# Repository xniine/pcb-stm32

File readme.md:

## A modified version of PCB to work with stm32-vserprog (to support 1.8v SPI)

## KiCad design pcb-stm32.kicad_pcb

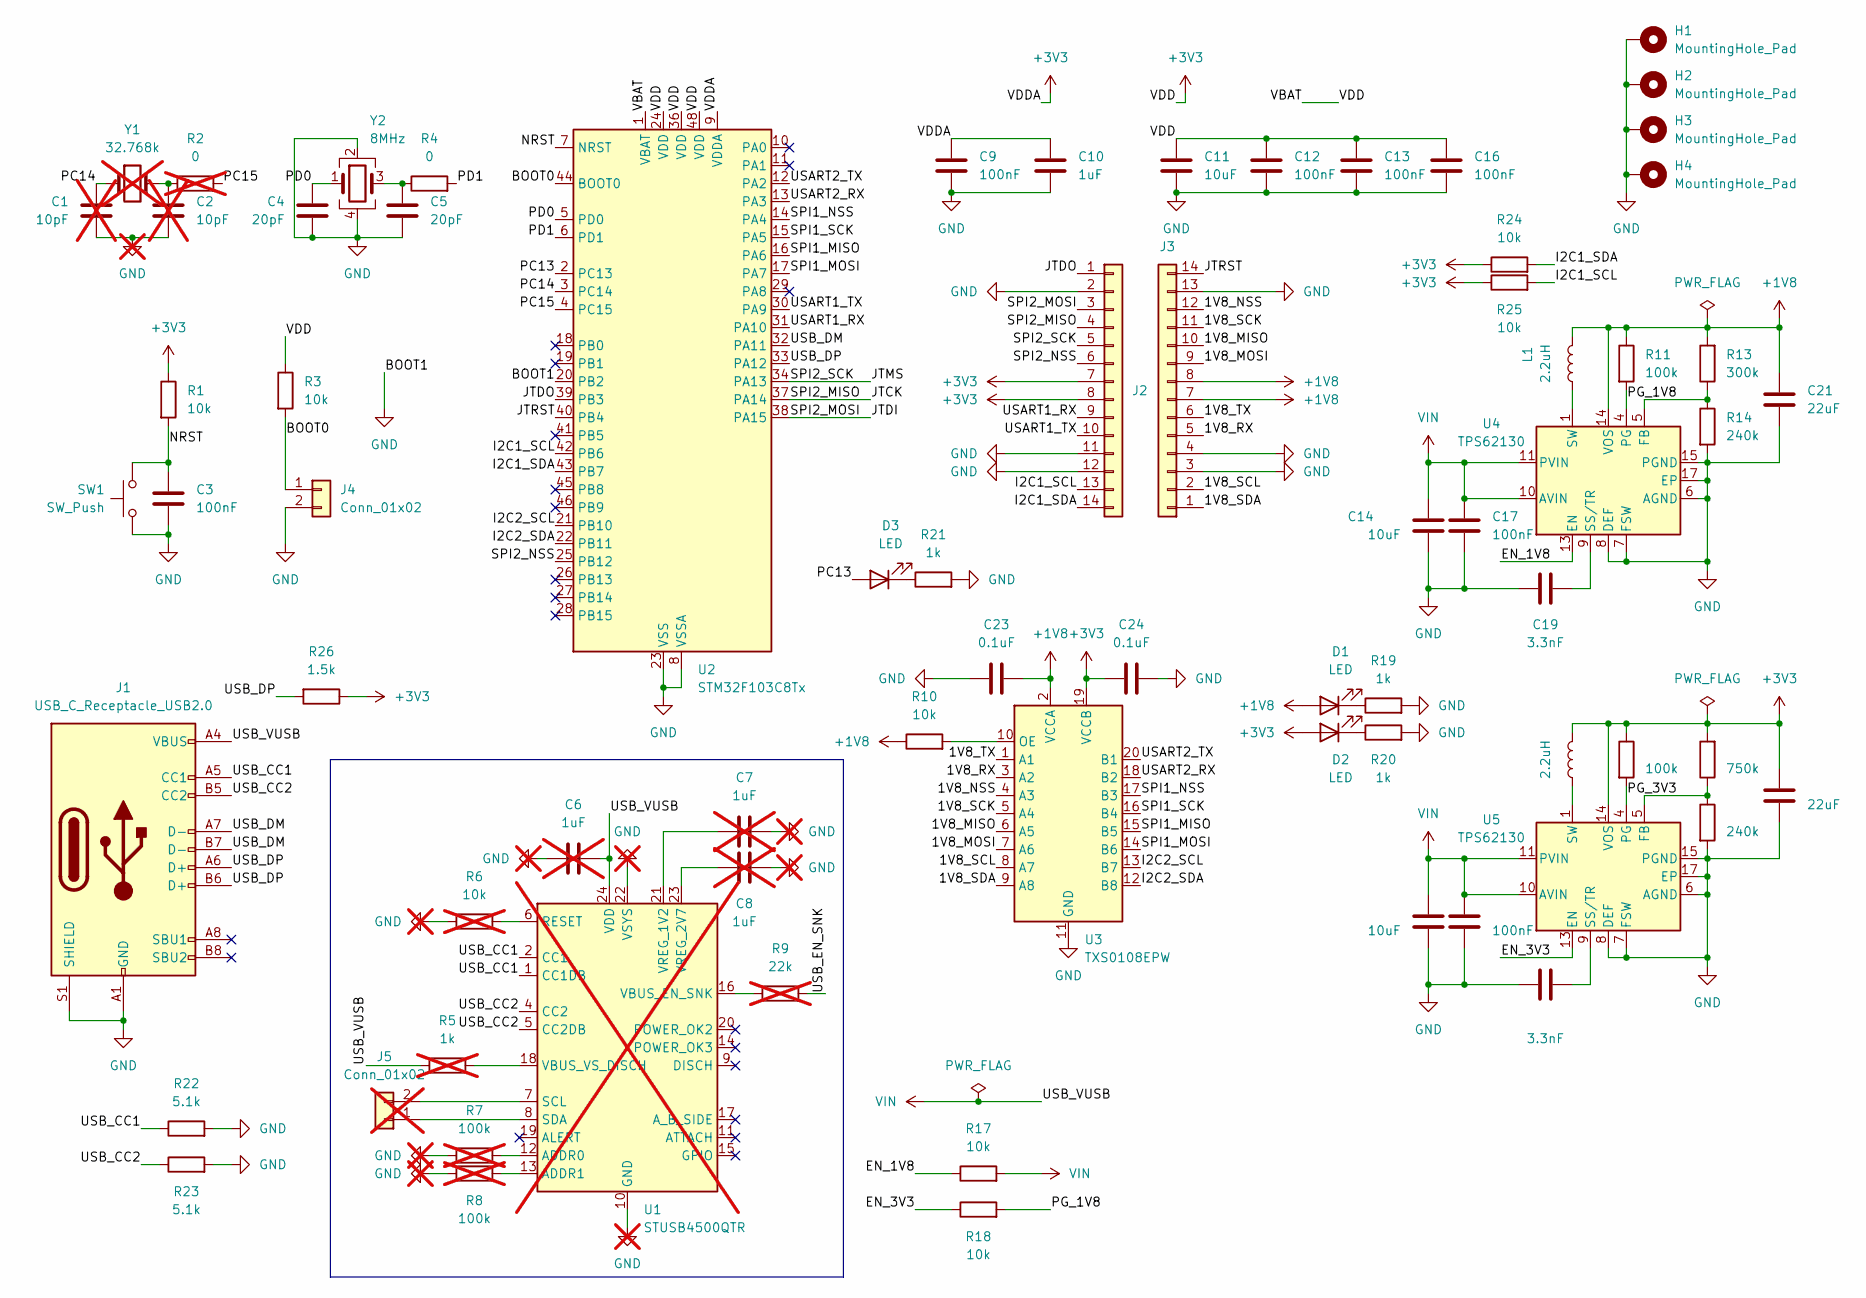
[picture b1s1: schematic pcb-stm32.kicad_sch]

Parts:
C1, C2: 10pF; C_0603_1608Metric; not fitted
C3, C9, C12, C13, C16, C17, C18: 100nF; C_0603_1608Metric
C4, C5: 20pF; C_0603_1608Metric
C6, C7, C8: 1uF; C_0603_1608Metric; not fitted
C10: 1uF; C_0603_1608Metric
C11, C14, C15: 10uF; C_0603_1608Metric
C19, C20: 3.3nF; C_0603_1608Metric
C21, C22: 22uF; C_0603_1608Metric
C23, C24: 0.1uF; C_0603_1608Metric
D1, D2, D3: LED; LED_0603_1608Metric
H1, H2, H3, H4: MountingHole_Pad; MountingHole_2.2mm_M2_Pad_Via
J1: USB_C_Receptacle_USB2.0; USB_C_Receptacle_G-Switch_GT-USB-7010ASV
J2, J3: PinHeader_1x14_P2.54mm_Horizontal
J4: Conn_01x02; PinHeader_1x02_P2.54mm_Vertical
J5: Conn_01x02; PinHeader_1x02_P1.27mm_Vertical; not fitted
L1, L2: 2.2uH; L_Coilcraft_XxL4020
R1, R3, R10, R17, R18, R24, R25: 10k; R_0603_1608Metric
R2: 0; R_0603_1608Metric; not fitted
R4: 0; R_0603_1608Metric
R5: 1k; R_0603_1608Metric; not fitted
R6: 10k; R_0603_1608Metric; not fitted
R7, R8: 100k; R_0603_1608Metric; not fitted
R9: 22k; R_0603_1608Metric; not fitted
R11, R12: 100k; R_0603_1608Metric
R13: 300k; R_0603_1608Metric
R14, R16: 240k; R_0603_1608Metric
R15: 750k; R_0603_1608Metric
R19, R20, R21: 1k; R_0603_1608Metric
R22, R23: 5.1k; R_0603_1608Metric
R26: 1.5k; R_0603_1608Metric
SW1: SW_Push; SW_PUSH_6mm
U1: STUSB4500QTR; QFN-24-1EP_4x4mm_P0.5mm_EP2.7x2.7mm; not fitted
U2: STM32F103C8Tx; LQFP-48_7x7mm_P0.5mm
U3: TXS0108EPW; TSSOP-20_4.4x6.5mm_P0.65mm
U4, U5: TPS62130; VQFN-16-1EP_3x3mm_P0.5mm_EP1.68x1.68mm_ThermalVias
Y1: 32.768k; Crystal_SMD_3215-2Pin_3.2x1.5mm; not fitted
Y2: 8MHz; Crystal_SMD_3225-4Pin_3.2x2.5mm

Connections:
+1V8: C21.1, C23.2, D1.2 (A), J3.7, J3.8, L1.2, R10.1, R11.1, R13.2, U3.2 (VCCA), U4.14 (VOS)
+3V3: C9.1, C10.1, C11.1, C12.1, C13.1, C16.1, C22.1, C24.2, D2.2 (A), J2.7, J2.8, L2.2, R1.1, R3.1, R12.1, R15.2, R24.1, R25.1, R26.1, U2.1 (VBAT), U2.9 (VDDA), U2.24 (VDD), U2.36 (VDD), U2.48 (VDD), U3.19 (VCCB), U5.14 (VOS)
/1V8_MISO: J3.10, U3.6 (A5)
/1V8_MOSI: J3.9, U3.7 (A6)
/1V8_NSS: J3.12, U3.4 (A3)
/1V8_RX: J3.5, U3.3 (A2)
/1V8_SCK: J3.11, U3.5 (A4)
/1V8_SCL: J3.2, U3.8 (A7)
/1V8_SDA: J3.1, U3.9 (A8)
/1V8_TX: J3.6, U3.1 (A1)
/BOOT0: J4.1, R3.2, U2.44 (BOOT0)
/EN_1V8: R17.1, U4.13 (EN)
/EN_3V3: R18.1, U5.13 (EN)
/I2C1_SCL: J2.13, R25.2, U2.42 (PB6)
/I2C1_SDA: J2.14, R24.2, U2.43 (PB7)
/I2C2_SCL: U2.21 (PB10), U3.13 (B7)
/I2C2_SDA: U2.22 (PB11), U3.12 (B8)
/JTCK: J2.4, U2.37 (PA14)
/JTDI: J2.3, U2.38 (PA15)
/JTDO: J2.1, U2.39 (PB3)
/JTMS: J2.5, U2.34 (PA13)
/JTRST: J3.14, U2.40 (PB4)
/NRST: C3.1, R1.2, SW1.2, U2.7 (NRST)
/PC13: D3.2 (A), U2.2 (PC13)
/PC14: C1.1, U2.3 (PC14), Y1.1
/PC15: R2.2, U2.4 (PC15)
/PD0: C4.1, U2.5 (PD0), Y2.1
/PD1: R4.2, U2.6 (PD1)
/PG_1V8: R11.2, R18.2, U4.4 (PG)
/PG_3V3: R12.2, U5.4 (PG)
/SPI1_MISO: U2.16 (PA6), U3.15 (B5)
/SPI1_MOSI: U2.17 (PA7), U3.14 (B6)
/SPI1_NSS: U2.14 (PA4), U3.17 (B3)
/SPI1_SCK: U2.15 (PA5), U3.16 (B4)
/SPI2_NSS: J2.6, U2.25 (PB12)
/USART1_RX: J2.9, U2.31 (PA10)
/USART1_TX: J2.10, U2.30 (PA9)
/USART2_RX: U2.13 (PA3), U3.18 (B2)
/USART2_TX: U2.12 (PA2), U3.20 (B1)
/USB_CC1: J1.A5 (CC1), R22.1, U1.1 (CC1DB), U1.2 (CC1)
/USB_CC2: J1.B5 (CC2), R23.1, U1.4 (CC2), U1.5 (CC2DB)
/USB_DM: J1.A7 (D-), J1.B7 (D-), U2.32 (PA11)
/USB_DP: J1.A6 (D+), J1.B6 (D+), R26.2, U2.33 (PA12)
/USB_EN_SNK: R9.2
GND: C1.2, C2.2, C3.2, C4.2, C5.2, C6.1, C7.1, C8.2, C9.2, C10.2, C11.2, C12.2, C13.2, C14.1, C15.1, C16.2, C17.2, C18.2, C19.1, C20.1, C21.2, C22.2, C23.1, C24.1, H1.1, H2.1, H3.1, H4.1, J1.A1 (GND), J1.A12 (GND), J1.B1 (GND), J1.B12 (GND), J1.S1 (SHIELD), J2.2, J2.11, J2.12, J3.3, J3.4, J3.13, J4.2, R6.2, R7.2, R8.2, R14.2, R16.2, R19.2, R20.2, R21.2, R22.2, R23.2, SW1.1, U1.10 (GND), U1.22 (VSYS), U1.25 (GND), U2.8 (VSSA), U2.20 (PB2), U2.23 (VSS), U2.35 (VSS), U2.47 (VSS), U3.11 (GND), U4.6 (AGND), U4.7 (FSW), U4.8 (DEF), U4.15 (PGND), U4.16 (PGND), U4.17 (EP), U5.6 (AGND), U5.7 (FSW), U5.8 (DEF), U5.15 (PGND), U5.16 (PGND), U5.17 (EP), Y2.2, Y2.4
unnamed: C2.1, R2.1, Y1.2
unnamed: C5.1, R4.1, Y2.3
unnamed: D1.1 (K), R19.1
unnamed: D2.1 (K), R20.1
unnamed: D3.1 (K), R21.1
unnamed: J5.1, U1.8 (SDA)
unnamed: J5.2, U1.7 (SCL)
unnamed: L1.1, U4.1 (SW), U4.2 (SW), U4.3 (SW)
unnamed: L2.1, U5.1 (SW), U5.2 (SW), U5.3 (SW)
unnamed: R7.1, U1.12 (ADDR0)
unnamed: R8.1, U1.13 (ADDR1)
unnamed: R6.1, U1.6 (RESET)
unnamed: R9.1, U1.16 (VBUS_EN_SNK)
unnamed: R5.1, U1.18 (VBUS_VS_DISCH)
unnamed: C7.2, U1.21 (VREG_1V2)
unnamed: C8.1, U1.23 (VREG_2V7)
unnamed: R10.2, U3.10 (OE)
unnamed: R13.1, R14.1, U4.5 (FB)
unnamed: C19.2, U4.9 (SS/TR)
unnamed: R15.1, R16.1, U5.5 (FB)
unnamed: C20.2, U5.9 (SS/TR)
VIN: C6.2, C14.2, C15.2, C17.1, C18.1, J1.A4 (VBUS), J1.A9 (VBUS), J1.B4 (VBUS), J1.B9 (VBUS), R5.2, R17.2, U1.24 (VDD), U4.10 (AVIN), U4.11 (PVIN), U4.12 (PVIN), U5.10 (AVIN), U5.11 (PVIN), U5.12 (PVIN)

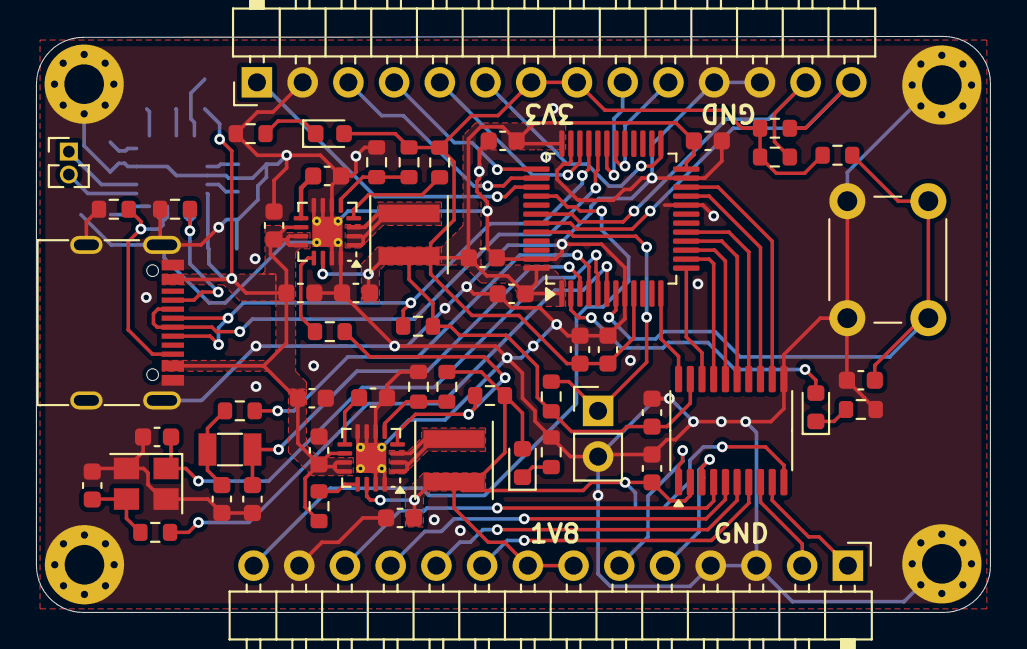
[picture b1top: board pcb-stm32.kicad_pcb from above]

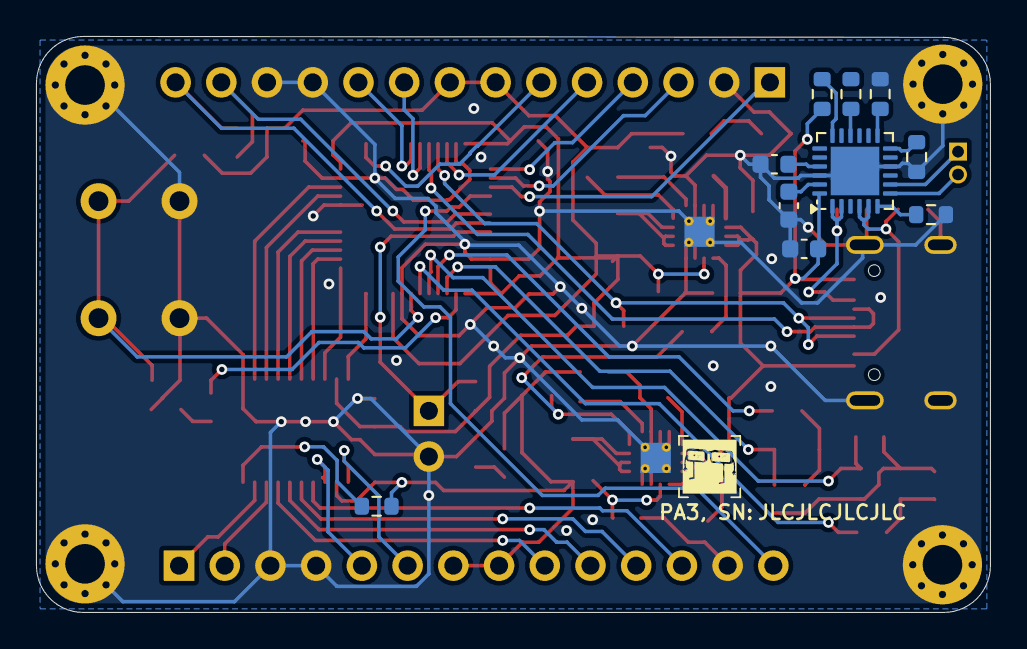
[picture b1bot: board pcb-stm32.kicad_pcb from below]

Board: 2 copper layers, 53.0 x 32.0 mm, 72 parts (10 on the bottom side), 66 nets.

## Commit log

2024-06-03 Push the project
